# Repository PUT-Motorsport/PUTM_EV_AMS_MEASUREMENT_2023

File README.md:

# PUTM_EV_AMS_MEASUREMENT_2023
BMS HV / AMS
Voltage & Temperature Measurement Board for PMX vehicle. Every cell voltage measurement is protected by a fuse.

### The research and development work was carried out was a part of the Student Scientific Clubs Create Innovations (SKNTI) program. [Ministry of Science and Higher Education](https://www.gov.pl/web/nauka)

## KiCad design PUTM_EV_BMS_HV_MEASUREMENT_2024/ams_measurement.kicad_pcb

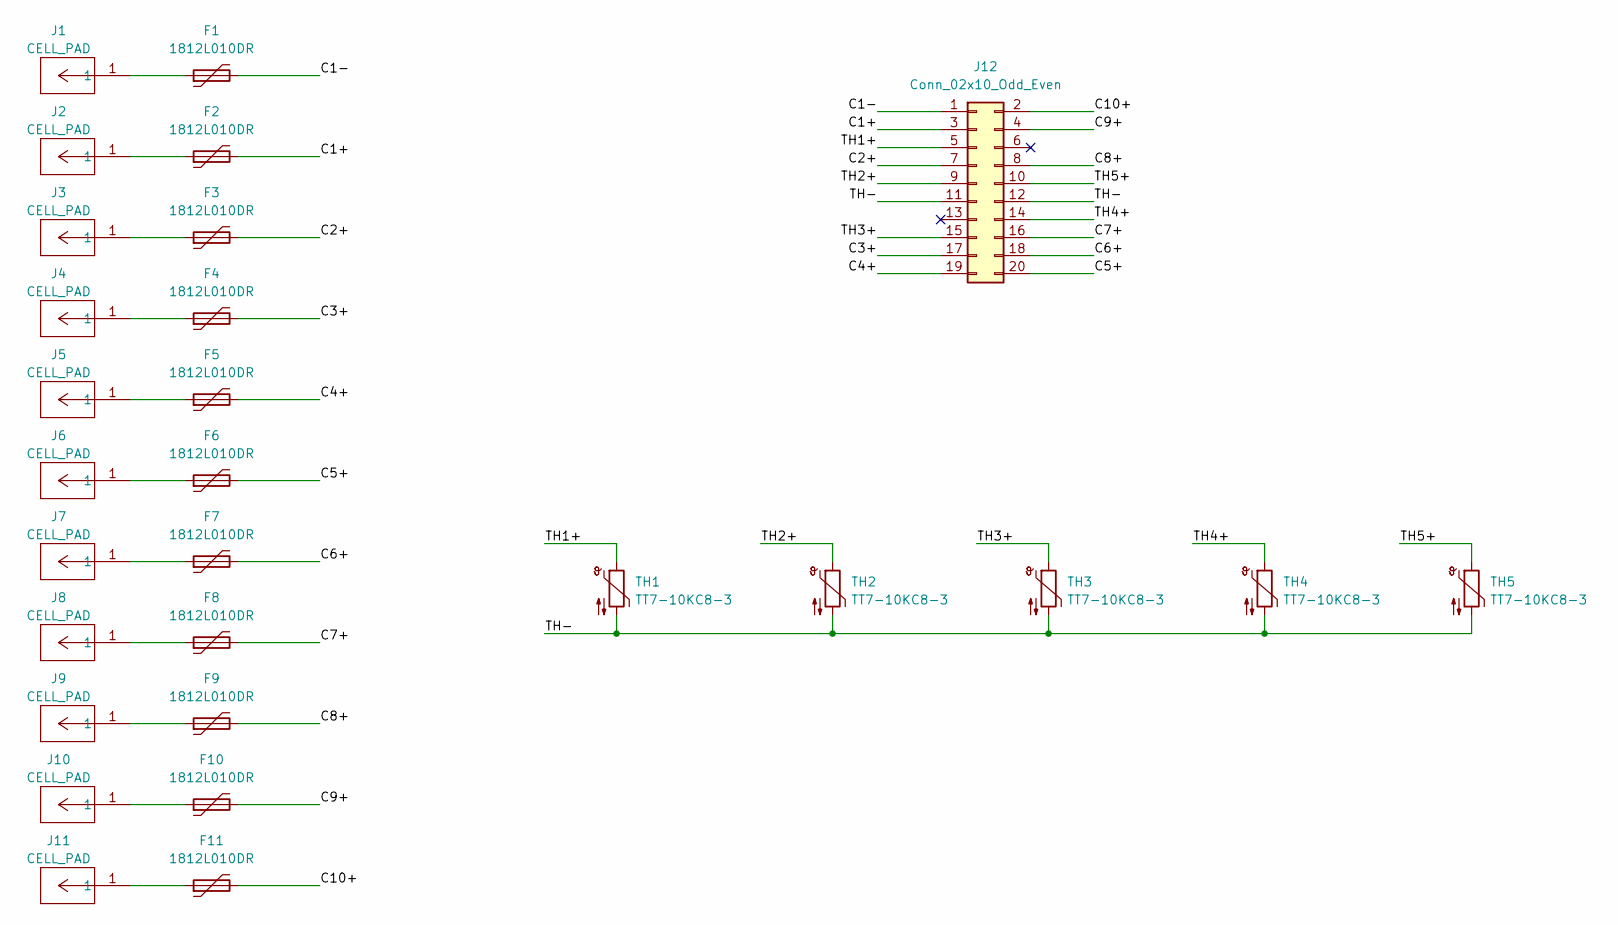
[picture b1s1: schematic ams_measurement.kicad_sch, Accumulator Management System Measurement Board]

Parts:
F1, F2, F3, F4, F5, F6, F7, F8, F9, F10, F11: 1812L010DR
J1, J2, J3, J4, J5, J6, J7, J8, J9, J10, J11: CELL_PAD; CONN_2065-100&slash_998-403_1_WAG
J12: Conn_02x10_Odd_Even; IDC-Header_2x10_P2.54mm_Vertical
TH1, TH2, TH3, TH4, TH5: TT7-10KC8-3; PinHeader_1x02_P2.54mm_Vertical

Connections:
/C1+: F2.2, J12.3
/C1-: F1.2, J12.1
/C2+: F3.2, J12.7
/C3+: F4.2, J12.17
/C4+: F5.2, J12.19
/C5+: F6.2, J12.20
/C6+: F7.2, J12.18
/C7+: F8.2, J12.16
/C8+: F9.2, J12.8
/C9+: F10.2, J12.4
/C10+: F11.2, J12.2
/TH1+: J12.5, TH1.1
/TH2+: J12.9, TH2.1
/TH3+: J12.15, TH3.1
/TH4+: J12.14, TH4.1
/TH5+: J12.10, TH5.1
/TH-: J12.11, J12.12, TH1.2, TH2.2, TH3.2, TH4.2, TH5.2
unnamed: F1.1, J1.1
unnamed: F2.1, J2.1
unnamed: F3.1, J3.1
unnamed: F4.1, J4.1
unnamed: F5.1, J5.1
unnamed: F6.1, J6.1
unnamed: F7.1, J7.1
unnamed: F8.1, J8.1
unnamed: F9.1, J9.1
unnamed: F10.1, J10.1
unnamed: F11.1, J11.1

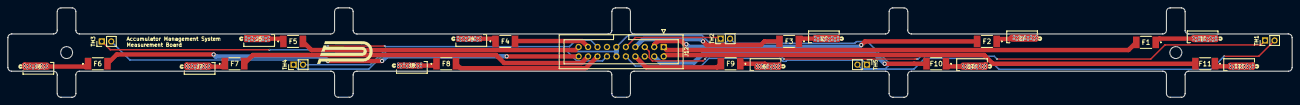
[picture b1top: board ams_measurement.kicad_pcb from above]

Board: 2 copper layers, 345.0 x 24.0 mm, 28 parts (0 on the bottom side), 28 nets.

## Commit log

2023-08-11 Update README.md
    added vehicle
2023-08-13 Changed connector to TE 5-5530843-0
2023-08-16 Revert "Changed connector to TE 5-5530843-0"
2023-10-18 Add files via upload
    2 symmetric / mirrored PCBs (A & B)
2023-11-03 Board outline changed
2023-11-05 Single PCB
2023-11-06 Changed thermistor position
2023-11-07 Wider tracks, vias and common -
    Tracks now 1.2mm
    Vias added to WAGO connector footprint
    All thermistors now have common negative pin
    Changes to thermistor placement (added TH5)
2023-11-16 Preparation for production
2023-11-16 Added components' datasheets
2024-04-26 Board dimensions changed
